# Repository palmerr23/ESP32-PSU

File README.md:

# ESP32-PSU

These files relate to a project published in Silicon Chip magazine in May/June 2021. https://www.siliconchip.com.au/

A general purpose ESP32 breakout board, optimised for lab instrument control, and a single channel hybrid power supply module.

Two separate versions of the Open Weather code are provided for the 2.8" and 3.5" display options. They should be compiled and loaded using your own OWM token. https://openweathermap.org/appid

For the Hybrid Power Supply, only compiled code is provided for 2.8" and 3.5" versions (ILI9341 and ILI9488 LCD controllers) because the number of libraries and complexity of code would make it difficult for others to get a clean compile.   

The Laser_Templates folder has SVG files for the front and rear panels of the power supply. There are separate versions for the 2.8" and 3.5" display options. In each front panel file there are two templates: the front panel itself (with colour coded cut [outlines] and etch [labels] elements) and a second template for a panel to support the display and controller PCBs (avoiding front panel screws). A reinforcing plate for the binding posts is also included. It is fitted behnd the front panel.

The front and supporting panels were cut from 2mm acrylic and the back panel from the plastic insert provided with the case.

The laser templates are designed for a Pro'skit 203-115B instrument case (Jaycar HB5910, Altronics H0482). The templates have been tested with LightBurn, but should work with other laser cutter software. 

My front panel was made with clear acrylic, coated on the BACK with black spray paint. Wood filler, in a contrasting colour, was squeegeed into the etched labels and then polished off with very fine DRY sandpaper (240 grit). A final coat of clear spray was then appled to seal the wood filler and restore a gloss finish to the acrylic.

The project can be compiled from source, with the usual caveats that external libraries may bnot be backward compatible.

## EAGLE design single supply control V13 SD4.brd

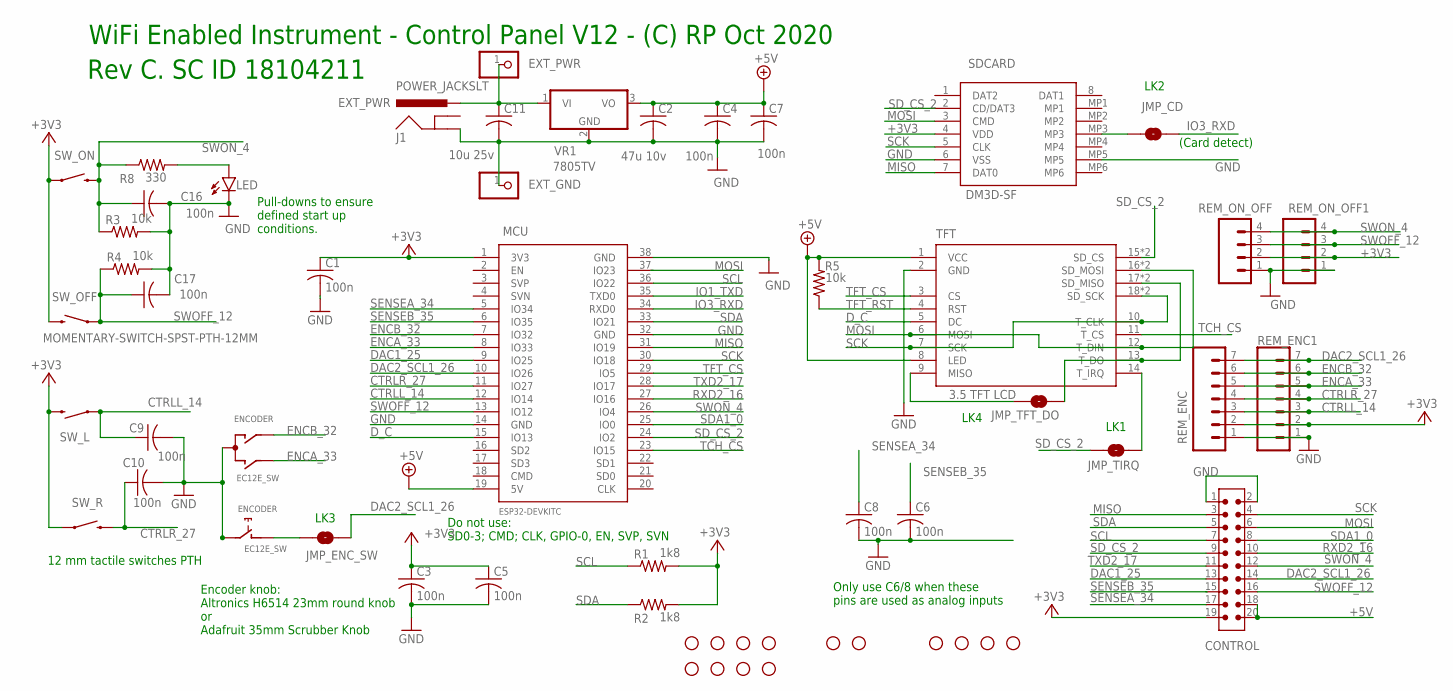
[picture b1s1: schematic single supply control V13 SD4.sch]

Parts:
C1, C3, C4, C5, C6, C7, C8, C9, C10, C16, C17: 100n; C0805K
C2: 47u 10v; C1210K
C11: 10u 25v; C1210K
CONTROL: 6120XX21621_61202021621; 61202021621
ENCODER: EC12E_SW; ALPS_EC12E_SW
EXT_GND: PINHD-1X1; 1X01
EXT_PWR: PINHD-1X1; 1X01
H1, H2, H3, H4, H5, H6, H7, H8, H9, H10, H11, H12, H13, H14: STAND-OFF
J1: POWER_JACKSLT; POWER_JACK_SLOT
JMP_CD: JUMPER-SMT_2_NO_SILK; SMT-JUMPER_2_NO_SILK
JMP_ENC_SW: JUMPER-SMT_2_NO_SILK; SMT-JUMPER_2_NO_SILK
JMP_TFT_DO: JUMPER-SMT_2_NO_SILK; SMT-JUMPER_2_NO_SILK
JMP_TIRQ: JUMPER-SMT_2_NO_SILK; SMT-JUMPER_2_NO_SILK
LED: LED3MM; LED_3MM
MCU: ESP32DEVKITC; ESP32-DEVKITC
R1, R2: 1k8; R0805W
R3, R4, R5: 10k; R0805W
R8: 330; R0805W
REM_ENC, REM_ENC1: CONN_07; 1X07
REM_ON_OFF, REM_ON_OFF1: CONN_04; 1X04
SDCARD: DM3D-SF; DM3DSF
SW_L: MOMENTARY-SWITCH-SPST-PTH-12MM; TACTILE_SWITCH_PTH_12MM
SW_OFF: MOMENTARY-SWITCH-SPST-PTH-12MM; TACTILE_SWITCH_PTH_12MM
SW_ON: MOMENTARY-SWITCH-SPST-PTH-12MM; TACTILE_SWITCH_PTH_12MM
SW_R: MOMENTARY-SWITCH-SPST-PTH-12MM; TACTILE_SWITCH_PTH_12MM
TFT: 2.8_3.5_TFT_TOUCH; 2.8_3.5_TFT_LCD
VR1: 7805TV; TO220V

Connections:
+3V3: C1.1, C3.1, C5.1, CONTROL.19, MCU.1 (3V3), R1.2, R2.2, REM_ENC.2, REM_ENC1.2, REM_ON_OFF.2, REM_ON_OFF1.2, SDCARD.4 (VDD), SW_L.3 (2), SW_OFF.3 (2), SW_ON.1, SW_R.1
+5V: C2.1, C4.1, C7.1, CONTROL.18, CONTROL.20, MCU.19 (5V), R5.2, TFT.1 (VCC), TFT.8 (LED), VR1.3 (VO)
CTRLL_14: C9.1, MCU.12 (IO14), REM_ENC.3, REM_ENC1.3, SW_L.1
CTRLR_27: C10.1, MCU.11 (IO27), REM_ENC.4, REM_ENC1.4, SW_R.3 (2)
DAC1_25: CONTROL.13, MCU.9 (IO25)
DAC2_SCL1_26: CONTROL.14, JMP_ENC_SW.2, MCU.10 (IO26), REM_ENC.7, REM_ENC1.7
D_C: MCU.15 (IO13), TFT.5 (DC)
ENCA_33: ENCODER.B, MCU.8 (IO33), REM_ENC.5, REM_ENC1.5
ENCB_32: ENCODER.A, MCU.7 (IO32), REM_ENC.6, REM_ENC1.6
ENC_SWX: ENCODER.D (1), JMP_ENC_SW.1
EXT_PWR: C11.1, EXT_PWR.1, J1.PWR, VR1.1 (VI)
GND: C1.2, C2.2, C3.2, C4.2, C5.2, C6.2, C7.2, C8.2, C9.2, C10.2, C11.2, C16.2, C17.2, CONTROL.1, CONTROL.2, ENCODER.C, ENCODER.E (2), EXT_GND.1, J1.GND@2 (GND), LED.K (C), MCU.14 (GND), MCU.32 (GND), MCU.38 (GND), R3.2, R4.2, REM_ENC.1, REM_ENC1.1, REM_ON_OFF.1, REM_ON_OFF1.1, SDCARD.6 (VSS), SDCARD.MP5, TFT.2 (GND), VR1.2 (GND)
IO1_TXD: MCU.35 (TXD0)
IO3_RXD: JMP_CD.2, MCU.34 (RXD0)
MISO: CONTROL.3, JMP_TFT_DO.2, MCU.31 (IO19), SDCARD.7 (DAT0), TFT.13 (T_DO), TFT.17 (SD_MISO), TFT.30 (SD_MISO)
MOSI: CONTROL.6, MCU.37 (IO23), SDCARD.3 (CMD), TFT.6 (MOSI), TFT.12 (T_DIN), TFT.16 (SD_MOSI), TFT.29 (SD_MOSI)
unnamed: JMP_CD.1, SDCARD.MP3
unnamed: JMP_TFT_DO.1, TFT.9 (MISO)
unnamed: JMP_TIRQ.2, TFT.14 (T_IRQ)
unnamed: LED.A, R8.2
RXD2_16: CONTROL.10, MCU.27 (IO16)
SCK: CONTROL.4, MCU.30 (IO18), SDCARD.5 (CLK), TFT.7 (SCK), TFT.10 (T_CLK), TFT.18 (SD_SCK), TFT.31 (SD_SCK)
SCL: CONTROL.7, MCU.36 (IO22), R1.1
SDA: CONTROL.5, MCU.33 (IO21), R2.1
SDA1_0: CONTROL.8, MCU.25 (IO0)
SD_CS_2: CONTROL.9, JMP_TIRQ.1, MCU.24 (IO2), SDCARD.2 (CD/DAT3), TFT.15 (SD_CS), TFT.28 (SD_CS)
SENSEA_34: C8.1, CONTROL.17, MCU.5 (IO34)
SENSEB_35: C6.1, CONTROL.15, MCU.6 (IO35)
SWOFF_12: C17.1, CONTROL.16, MCU.13 (IO12), R4.1, REM_ON_OFF.3, REM_ON_OFF1.3, SW_OFF.1
SWON_4: C16.1, CONTROL.12, MCU.26 (IO4), R3.1, R8.1, REM_ON_OFF.4, REM_ON_OFF1.4, SW_ON.3 (2)
TCH_CS: MCU.23 (IO15), TFT.11 (T_CS)
TFT_CS: MCU.29 (IO5), TFT.3 (CS)
TFT_RST: R5.1, TFT.4 (RST)
TXD2_17: CONTROL.11, MCU.28 (IO17)

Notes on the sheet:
Pull-downs to ensure defined start up conditions.
12 mm tactile switches PTH
Encoder knob: Altronics H6514 23mm round knob or Adafruit 35mm Scrubber Knob
Only use C6/8 when these pins are used as analog inputs
WiFi Enabled Instrument - Control Panel V12 - (C) RP Oct 2020
Do not use: SD0-3; CMD; CLK, GPIO-0, EN, SVP, SVN
Rev C. SC ID 18104211
(Card detect)
LK4
LK1
LK2
LK3

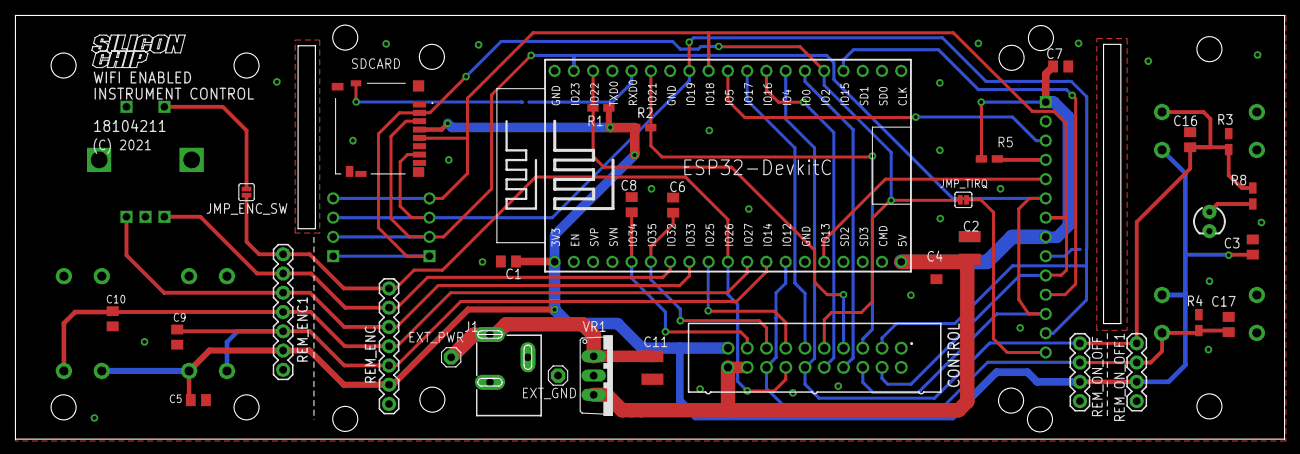
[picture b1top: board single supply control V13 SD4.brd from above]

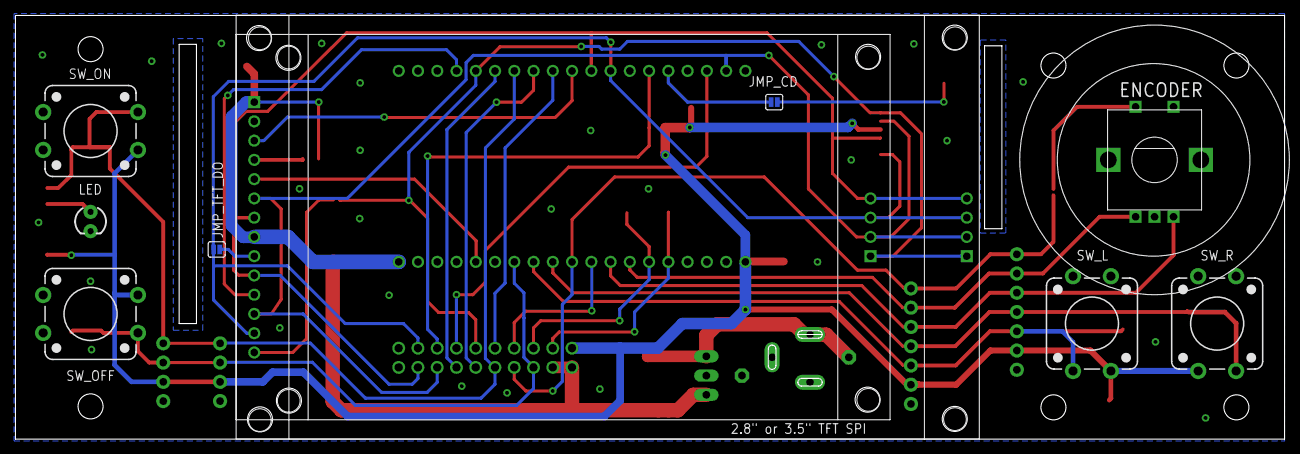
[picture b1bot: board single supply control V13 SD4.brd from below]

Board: 2 copper layers, 167.4 x 55.8 mm, 55 parts (9 on the bottom side), 33 nets.

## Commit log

2021-02-05 Add files via upload
    Improve heat management
2021-02-05 Add files via upload
    First production version of PSU code
2021-06-04 3.5" screen option
2021-06-07 Added 3.5" Power Supply code variant
2021-06-07 Fixed item locations on Comms menu
2021-06-07 Added eagle files
2022-01-06 Supercedes Control_C_ADS_Touch v1-0.ino.bin for 2.8" displays
2022-01-06 Minor changes. Fan pin confirmed as GPIO 26 / Control pin 14
2022-01-07 Added tutorial reference
2025-01-03 Source upload
2025-01-05 Added fonts
2025-01-06 Rename directory as required by IDE
2025-01-06 Rename file to avoid compiler error
2025-01-06 Use quotes to avoid compiler errors
2025-01-06 Updated source
2025-01-06 Move the project back into the source directory
2025-01-08 Initial support for building in PlatformIO
2025-01-08 Don't track files copied from Arduino sketch
2025-01-08 Run over-the-air update from PlatformIO
2025-01-08 Add compile instructions
2025-01-08 Remove Arduino core libraries from platformio.ini
2025-01-08 Add instructions for using PlatformIO
2025-01-08 Add fan hysteresis

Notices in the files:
single supply control V13 SD4.brd:
(C) 2021
parts and their libraries:
SparkFun-Hardware: Licensing: Creative Commons ShareAlike 4.0 International - https://creativecommons.org/licenses/by-sa/4.0
Wurth_Connectors_WR-BHD: Copyright: Würth Elektronik
